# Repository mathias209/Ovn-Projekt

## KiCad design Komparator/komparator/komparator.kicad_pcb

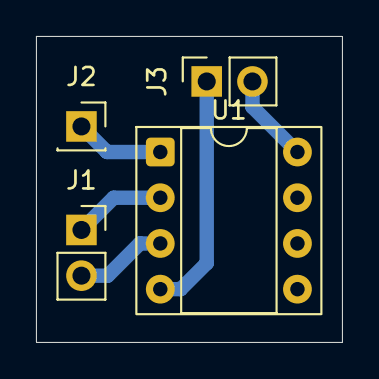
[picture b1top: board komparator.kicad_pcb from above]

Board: 2 copper layers, 17.0 x 17.0 mm, 4 parts (0 on the bottom side), 5 nets.

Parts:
J1, J3: Conn_01x02_Socket; PinSocket_1x02_P2.54mm_Vertical
J2: Conn_01x01_Socket; PinSocket_1x01_P2.54mm_Vertical
U1: MCP6002-xP; DIP-8_W7.62mm_Socket

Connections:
+5V: J3.2, U1.8 (V+)
GND: J3.1, U1.4 (V-)
unnamed: J1.1, U1.2 (-)
unnamed: J1.2, U1.3 (+)
unnamed: J2.1, U1.1

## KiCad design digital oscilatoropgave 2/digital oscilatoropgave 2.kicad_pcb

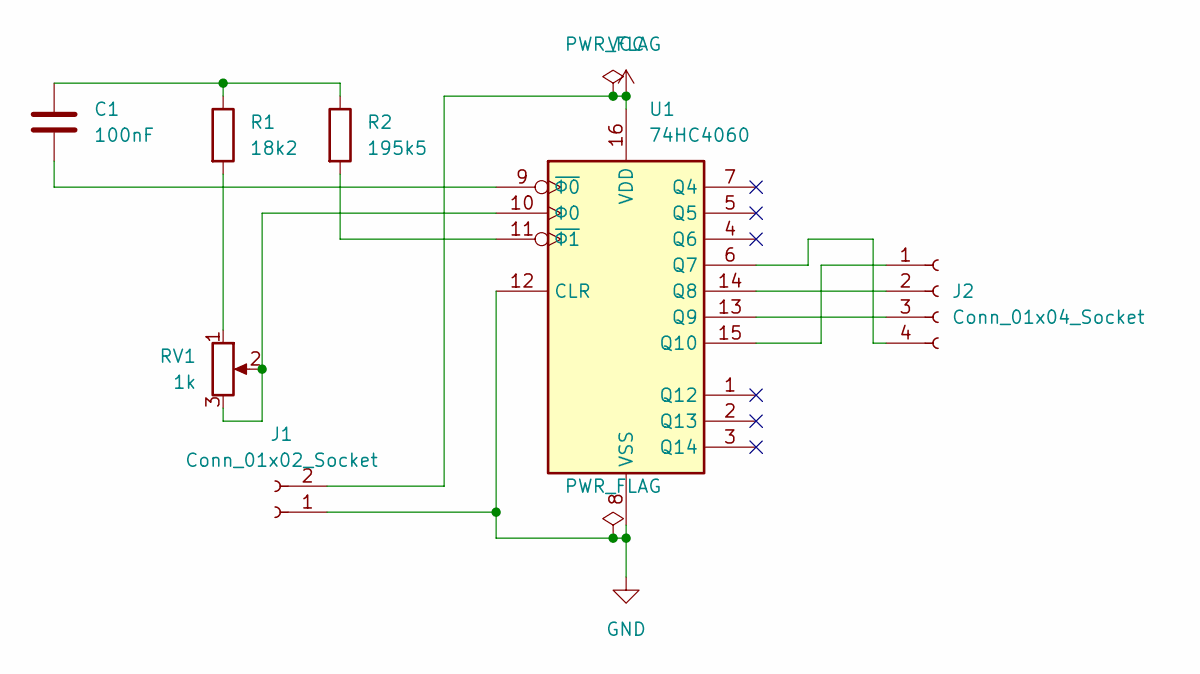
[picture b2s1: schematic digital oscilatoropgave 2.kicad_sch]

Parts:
C1: 100nF; C_Disc_D7.0mm_W2.5mm_P5.00mm
J1: Conn_01x02_Socket; JWT_A3963_1x02_P3.96mm_Vertical
J2: Conn_01x04_Socket; PinSocket_1x04_P2.54mm_Vertical
R1: 18k2; R_Axial_DIN0207_L6.3mm_D2.5mm_P10.16mm_Horizontal
R2: 195k5; R_Axial_DIN0207_L6.3mm_D2.5mm_P10.16mm_Horizontal
RV1: 1k; Potentiometer_ACP_CA9-V10_Vertical
U1: 74HC4060; DIP-16_W7.62mm_Socket

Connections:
GND: J1.1, U1.8 (VSS), U1.12 (CLR)
unnamed: C1.1, R1.1, R2.1
unnamed: J2.1, U1.15 (Q10)
unnamed: J2.2, U1.14 (Q8)
unnamed: J2.3, U1.13 (Q9)
unnamed: J2.4, U1.6 (Q7)
unnamed: R1.2, RV1.1
unnamed: C1.2, U1.9 (~Φ0)
unnamed: R2.2, U1.11 (~Φ1)
unnamed: RV1.2, RV1.3, U1.10 (Φ0)
VCC: J1.2, U1.16 (VDD)

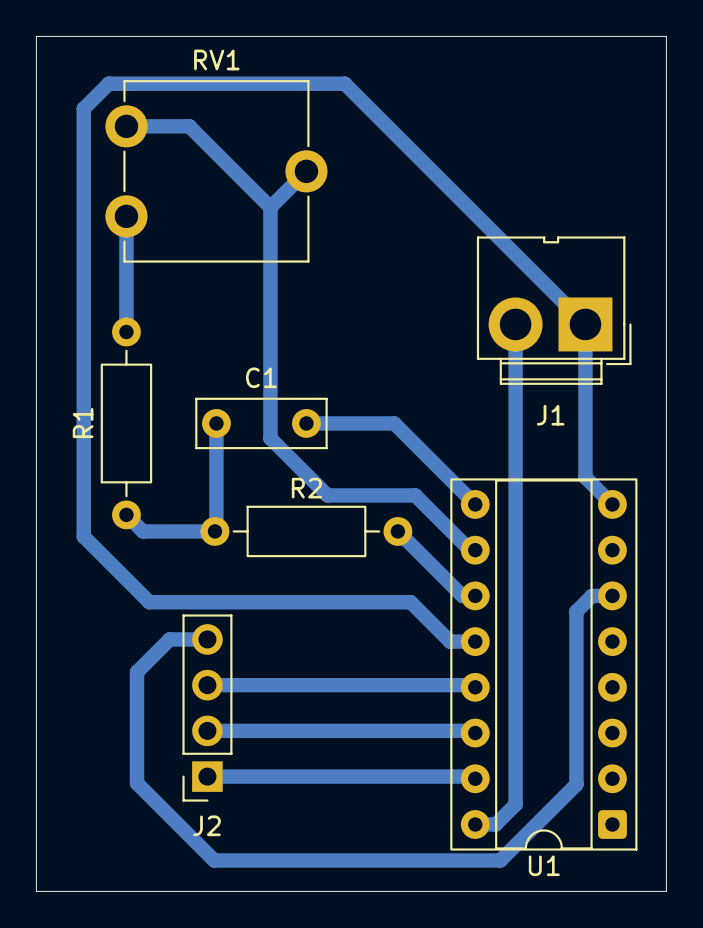
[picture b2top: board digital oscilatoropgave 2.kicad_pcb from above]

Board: 2 copper layers, 35.0 x 47.5 mm, 7 parts (0 on the bottom side), 11 nets.

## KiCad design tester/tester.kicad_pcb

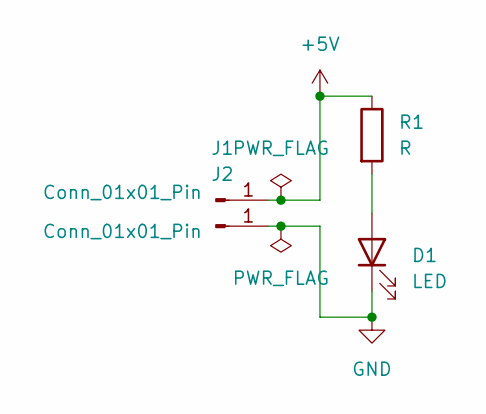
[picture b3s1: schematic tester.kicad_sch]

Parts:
D1: LED; LED_D1.8mm_W1.8mm_H2.4mm_Horizontal_O6.35mm_Z1.6mm
J1, J2: Conn_01x01_Pin; Pin_D1.0mm_L10.0mm
R1: R; R_Axial_DIN0207_L6.3mm_D2.5mm_P7.62mm_Horizontal

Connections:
+5V: J1.1, R1.1
GND: D1.1 (K), J2.1
unnamed: D1.2 (A), R1.2

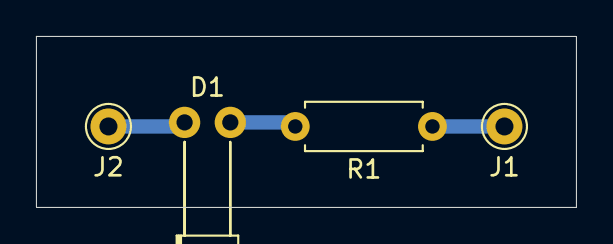
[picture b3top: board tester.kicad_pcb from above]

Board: 2 copper layers, 30.0 x 9.5 mm, 4 parts (0 on the bottom side), 3 nets.
